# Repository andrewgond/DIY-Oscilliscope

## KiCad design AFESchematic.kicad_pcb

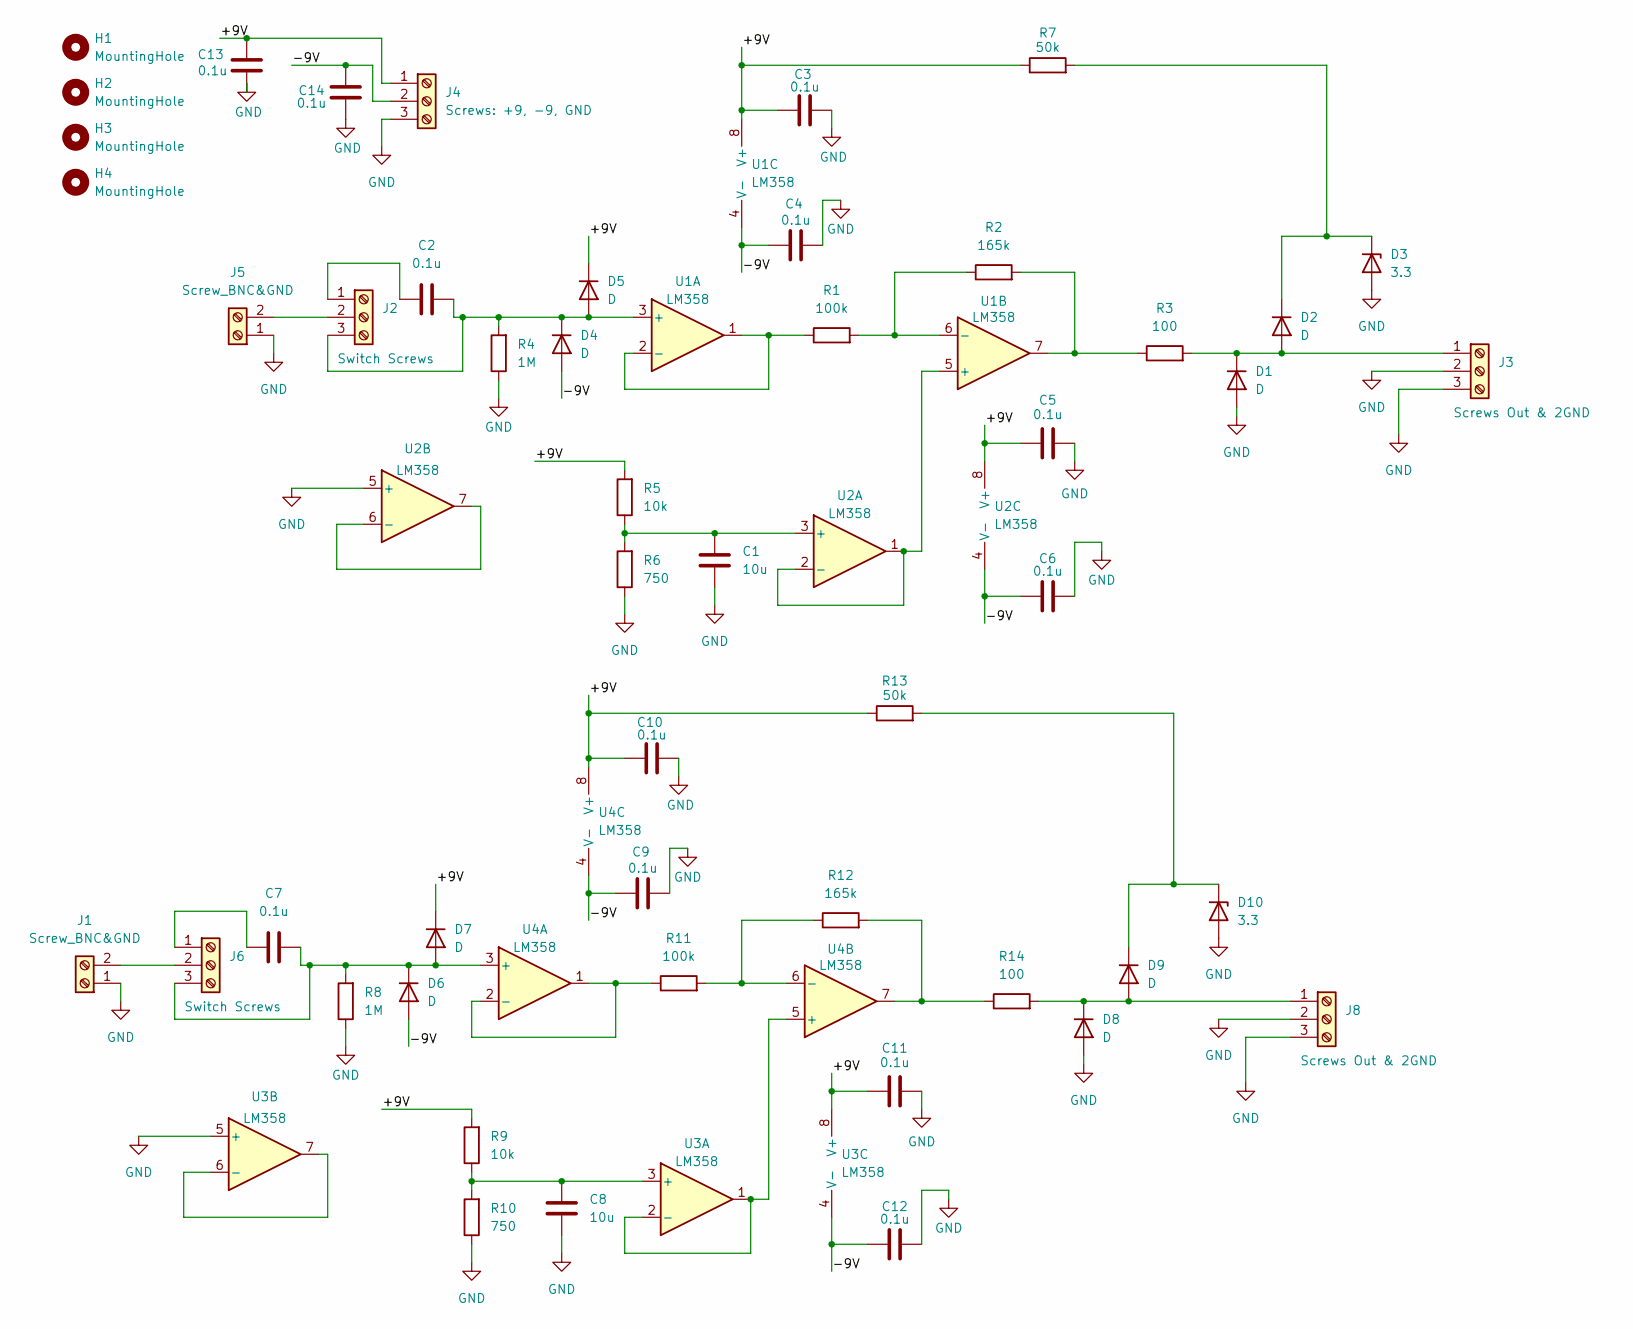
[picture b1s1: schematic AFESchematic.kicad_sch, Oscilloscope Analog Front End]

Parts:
C1, C8: 10u; C_0603_1608Metric
C2, C3, C4, C5, C6, C7, C9, C10, C11, C12, C13, C14: 0.1u; C_0603_1608Metric
D1, D2, D4, D5, D6, D7, D8, D9: D; D_SOD-523
D3, D10: 3.3; D_SOD-123
H1, H2, H3, H4: MountingHole; MountingHole_2.1mm
J1, J5: Screw_BNC&GND; 2ScrewTerm
J2, J6: Switch Screws; 3ScrewTerm
J3, J8: Screws Out & 2GND; 3ScrewTerm
J4: Screws: +9, -9, GND; 3ScrewTerm
R1, R11: 100k; R_0603_1608Metric
R2, R12: 165k; R_0603_1608Metric
R3, R14: 100; R_0603_1608Metric
R4, R8: 1M; R_0603_1608Metric
R5, R9: 10k; R_0603_1608Metric
R6, R10: 750; R_0603_1608Metric
R7, R13: 50k; R_0603_1608Metric
U1, U2, U3, U4: LM358; SOIC127P599X175-8N

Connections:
/+9V: C3.2, C5.2, C10.2, C11.2, C13.2, D5.1 (K), D7.1 (K), J4.1, R5.2, R7.1, R9.2, R13.1, U1.8 (V+), U2.8 (V+), U3.8 (V+), U4.8 (V+)
/-9V: C4.2, C6.2, C9.2, C12.2, C14.2, D4.2 (A), D6.2 (A), J4.2, U1.4 (V-), U2.4 (V-), U3.4 (V-), U4.4 (V-)
GND: C1.1, C3.1, C4.1, C5.1, C6.1, C8.1, C9.1, C10.1, C11.1, C12.1, C13.1, C14.1, D1.2 (A), D3.2 (A), D8.2 (A), D10.2 (A), J1.1, J3.2, J3.3, J4.3, J5.1, J8.2, J8.3, R4.1, R6.1, R8.1, R10.1, U2.5 (+), U3.5 (+)
unnamed: D1.1 (K), D2.2 (A), J3.1, R3.2
unnamed: D2.1 (K), D3.1 (K), R7.2
unnamed: C2.1, D4.1 (K), D5.2 (A), J2.3, R4.2, U1.3 (+)
unnamed: C7.1, D6.1 (K), D7.2 (A), J6.3, R8.2, U4.3 (+)
unnamed: D8.1 (K), D9.2 (A), J8.1, R14.2
unnamed: D9.1 (K), D10.1 (K), R13.2
unnamed: J1.2, J6.2
unnamed: C2.2, J2.1
unnamed: J2.2, J5.2
unnamed: C7.2, J6.1
unnamed: R2.2, R3.1, U1.7
unnamed: R12.2, R14.1, U4.7
unnamed: R1.1, U1.1, U1.2 (-)
unnamed: U1.5 (+), U2.1, U2.2 (-)
unnamed: R1.2, R2.1, U1.6 (-)
unnamed: C1.2, R5.1, R6.2, U2.3 (+)
unnamed: U2.6 (-), U2.7
unnamed: C8.2, R9.1, R10.2, U3.3 (+)
unnamed: U3.1, U3.2 (-), U4.5 (+)
unnamed: U3.6 (-), U3.7
unnamed: R11.1, U4.1, U4.2 (-)
unnamed: R11.2, R12.1, U4.6 (-)

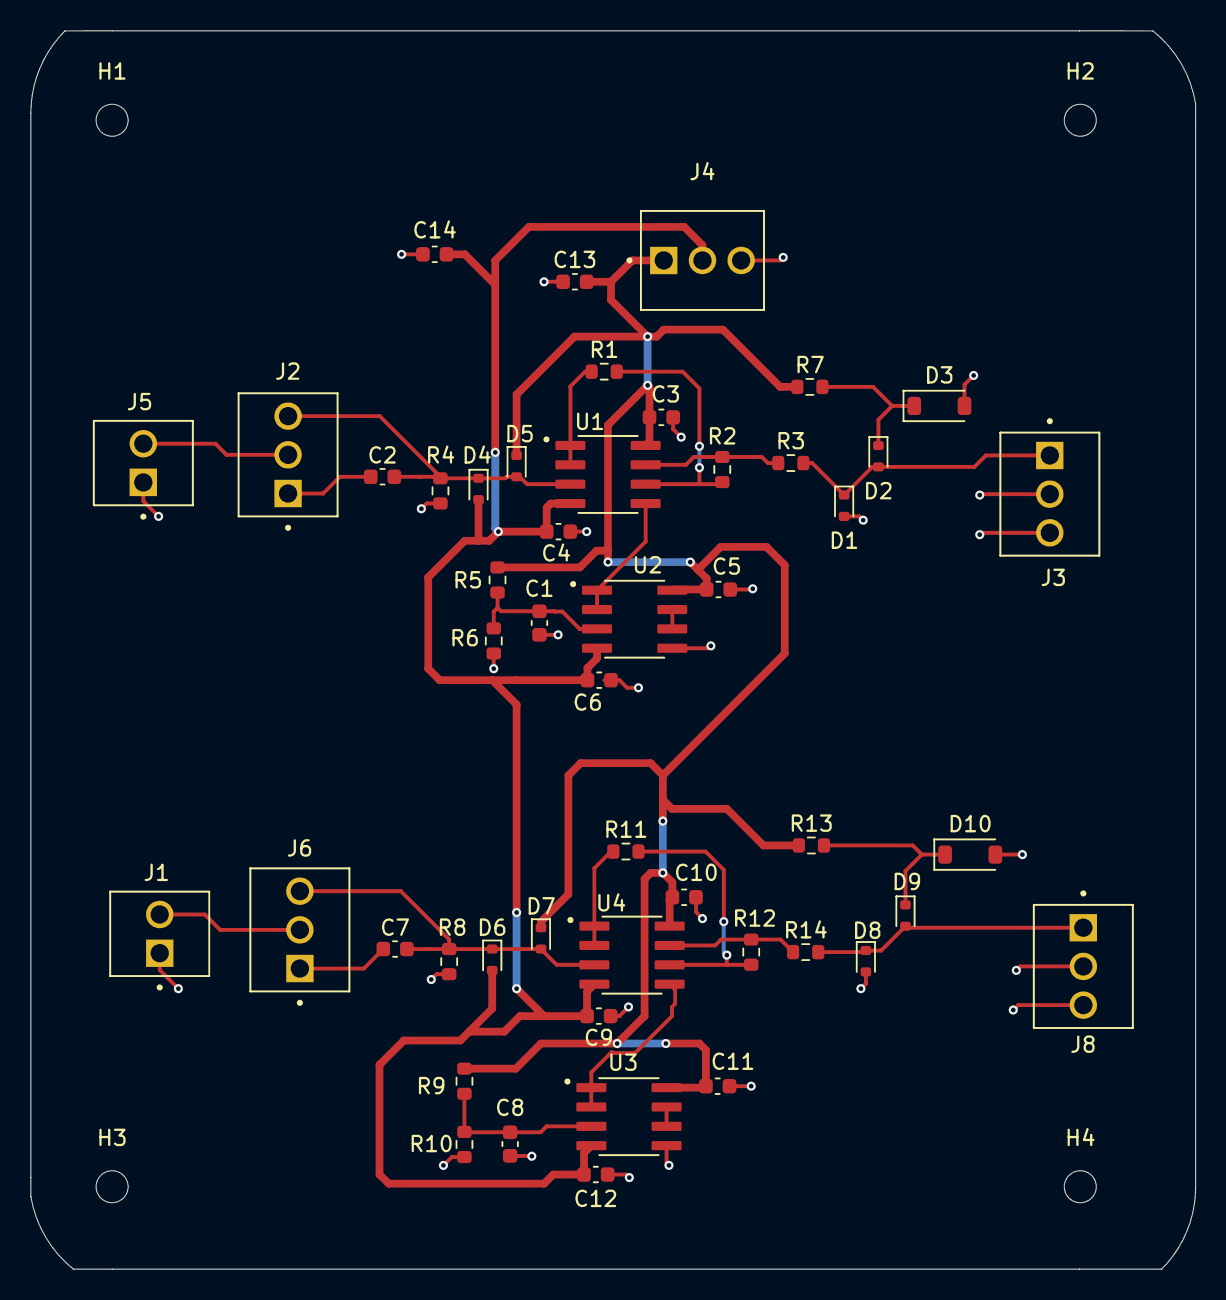
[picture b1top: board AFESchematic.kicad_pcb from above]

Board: 2 copper layers, 76.5 x 81.3 mm, 53 parts (0 on the bottom side), 25 nets.

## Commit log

2025-11-23 Rename arduinocode/JD_Oscilliscope_code.ino to Oscilliscope_code.ino
2025-11-23 Rename Oscilloscope-system-documentation.pdf to Documentation/Oscilloscope-system-documentation.pdf
